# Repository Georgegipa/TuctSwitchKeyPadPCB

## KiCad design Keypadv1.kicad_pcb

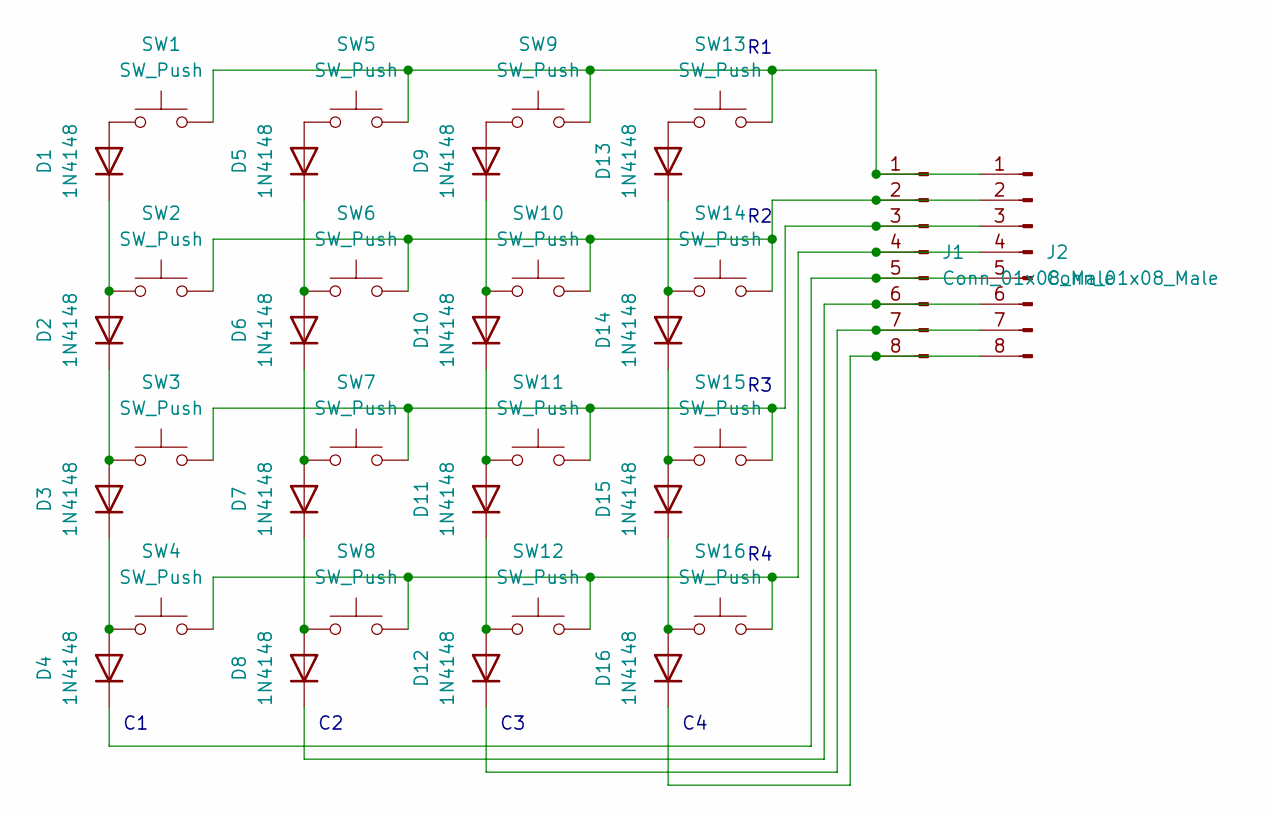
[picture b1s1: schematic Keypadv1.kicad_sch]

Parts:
D1, D2, D3, D4, D5, D6, D7, D8, D9, D10, D11, D12, D13, D14, D15, D16: 1N4148; D_DO-35_SOD27_P7.62mm_Horizontal
J1, J2: Conn_01x08_Male; PinHeader_1x08_P2.54mm_Vertical
SW1, SW2, SW3, SW4, SW5, SW6, SW7, SW8, SW9, SW10, SW11, SW12, SW13, SW14, SW15, SW16: SW_Push; SW_PUSH-12mm

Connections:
unnamed: D1.1 (K), D2.2 (A), SW2.1
unnamed: D1.2 (A), SW1.1
unnamed: D2.1 (K), D3.2 (A), SW3.1
unnamed: D3.1 (K), D4.2 (A), SW4.1
unnamed: D4.1 (K), J1.5, J2.5
unnamed: D5.1 (K), D6.2 (A), SW6.1
unnamed: D5.2 (A), SW5.1
unnamed: D6.1 (K), D7.2 (A), SW7.1
unnamed: D7.1 (K), D8.2 (A), SW8.1
unnamed: D8.1 (K), J1.6, J2.6
unnamed: D9.2 (A), SW9.1
unnamed: D10.1 (K), D11.2 (A), SW11.1
unnamed: D9.1 (K), D10.2 (A), SW10.1
unnamed: D11.1 (K), D12.2 (A), SW12.1
unnamed: D12.1 (K), J1.7, J2.7
unnamed: D13.1 (K), D14.2 (A), SW14.1
unnamed: D13.2 (A), SW13.1
unnamed: D14.1 (K), D15.2 (A), SW15.1
unnamed: D15.1 (K), D16.2 (A), SW16.1
unnamed: D16.1 (K), J1.8, J2.8
unnamed: J1.1, J2.1, SW1.2, SW5.2, SW9.2, SW13.2
unnamed: J1.2, J2.2, SW2.2, SW6.2, SW10.2, SW14.2
unnamed: J1.3, J2.3, SW3.2, SW7.2, SW11.2, SW15.2
unnamed: J1.4, J2.4, SW4.2, SW8.2, SW12.2, SW16.2

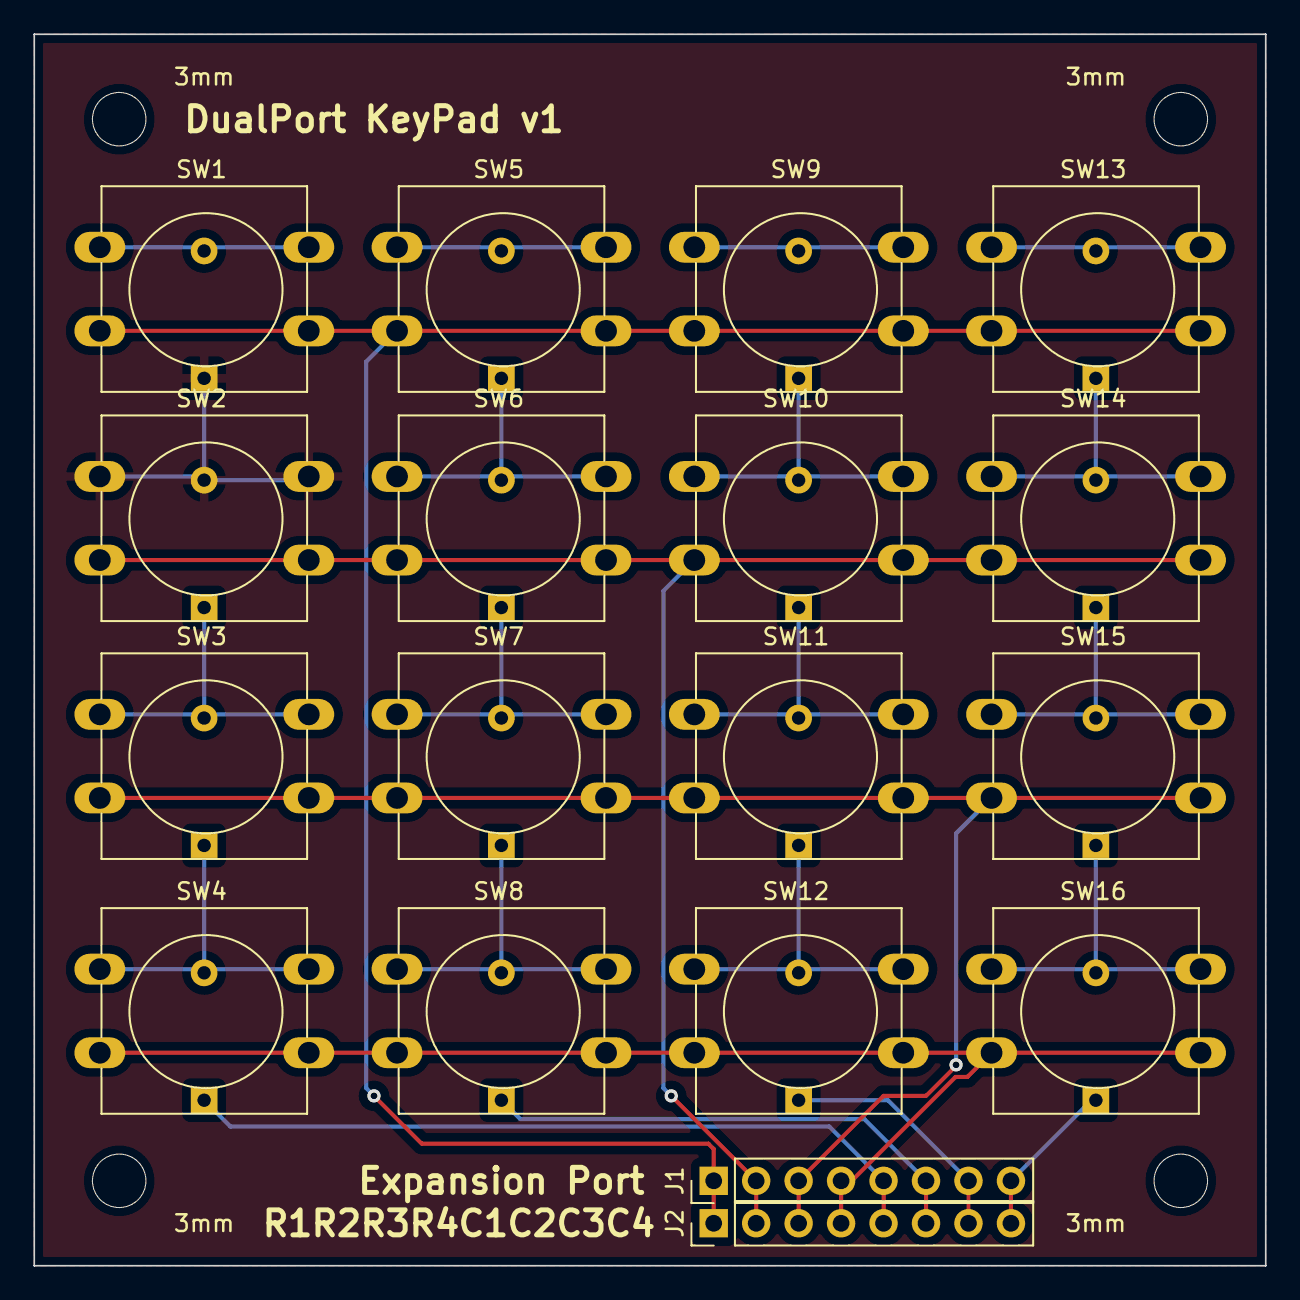
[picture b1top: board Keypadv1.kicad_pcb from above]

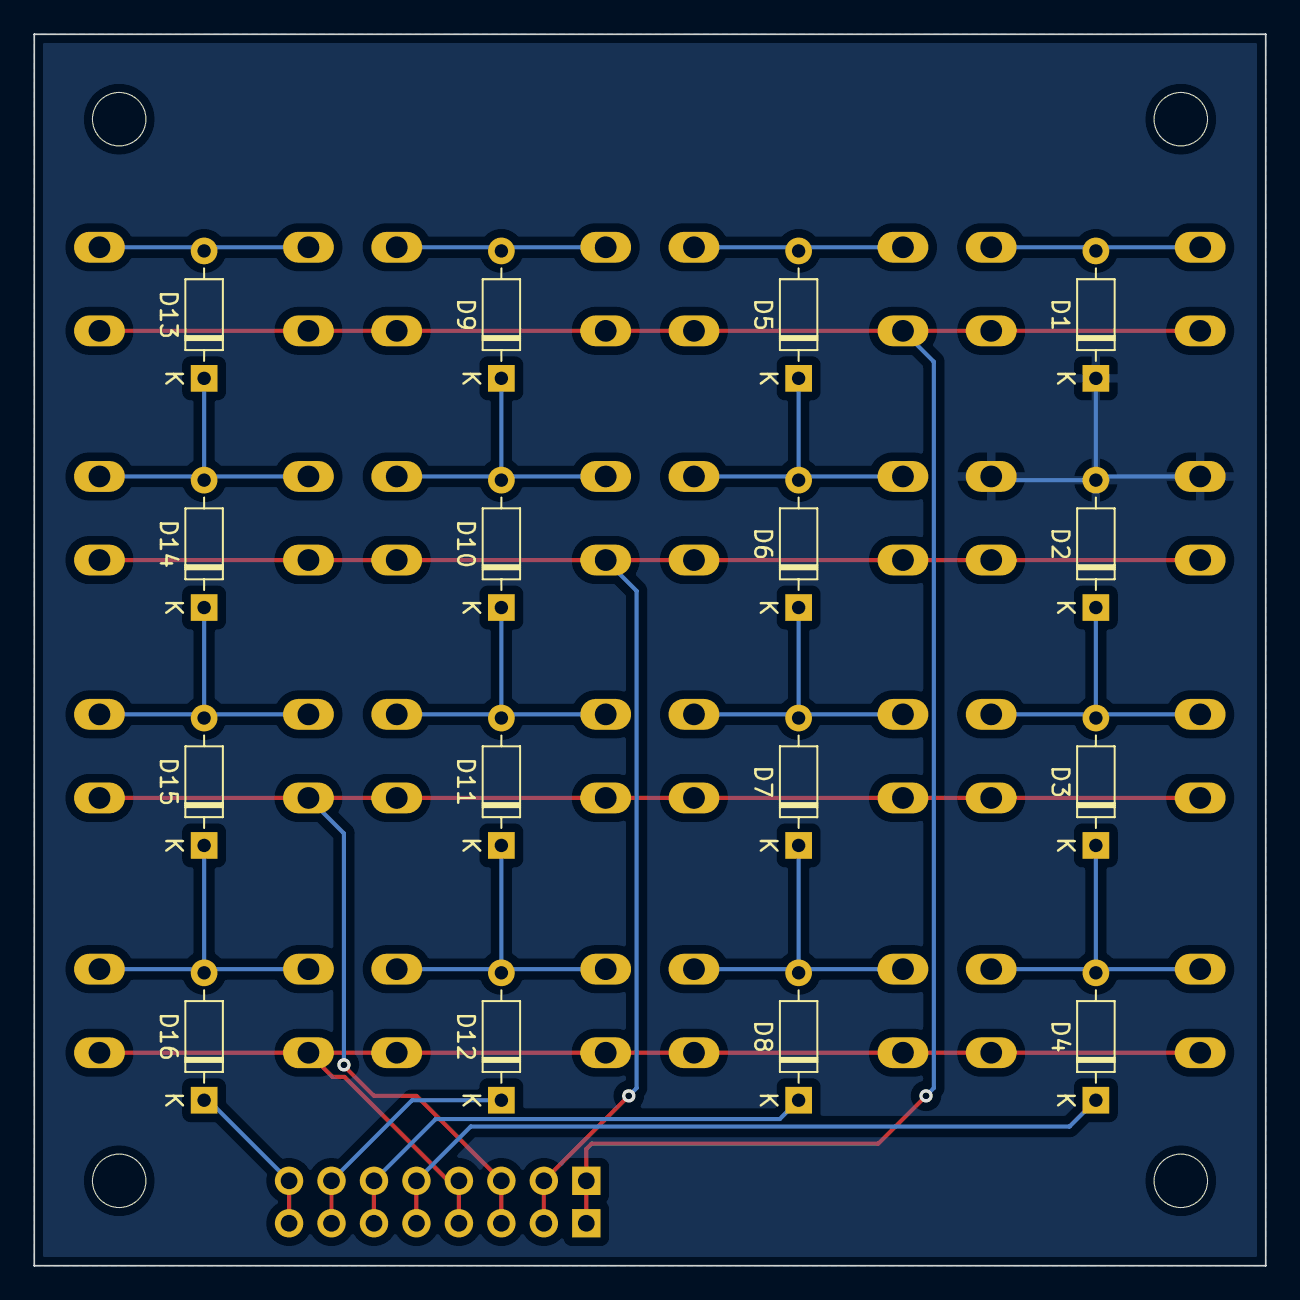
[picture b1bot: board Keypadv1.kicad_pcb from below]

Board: 2 copper layers, 73.7 x 73.7 mm, 38 parts (16 on the bottom side), 24 nets.

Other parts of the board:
3mm, 3mm#2, 3mm#3, 3mm#4: MountingHole_3.2mm_M3

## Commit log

2022-01-27 1st commit
